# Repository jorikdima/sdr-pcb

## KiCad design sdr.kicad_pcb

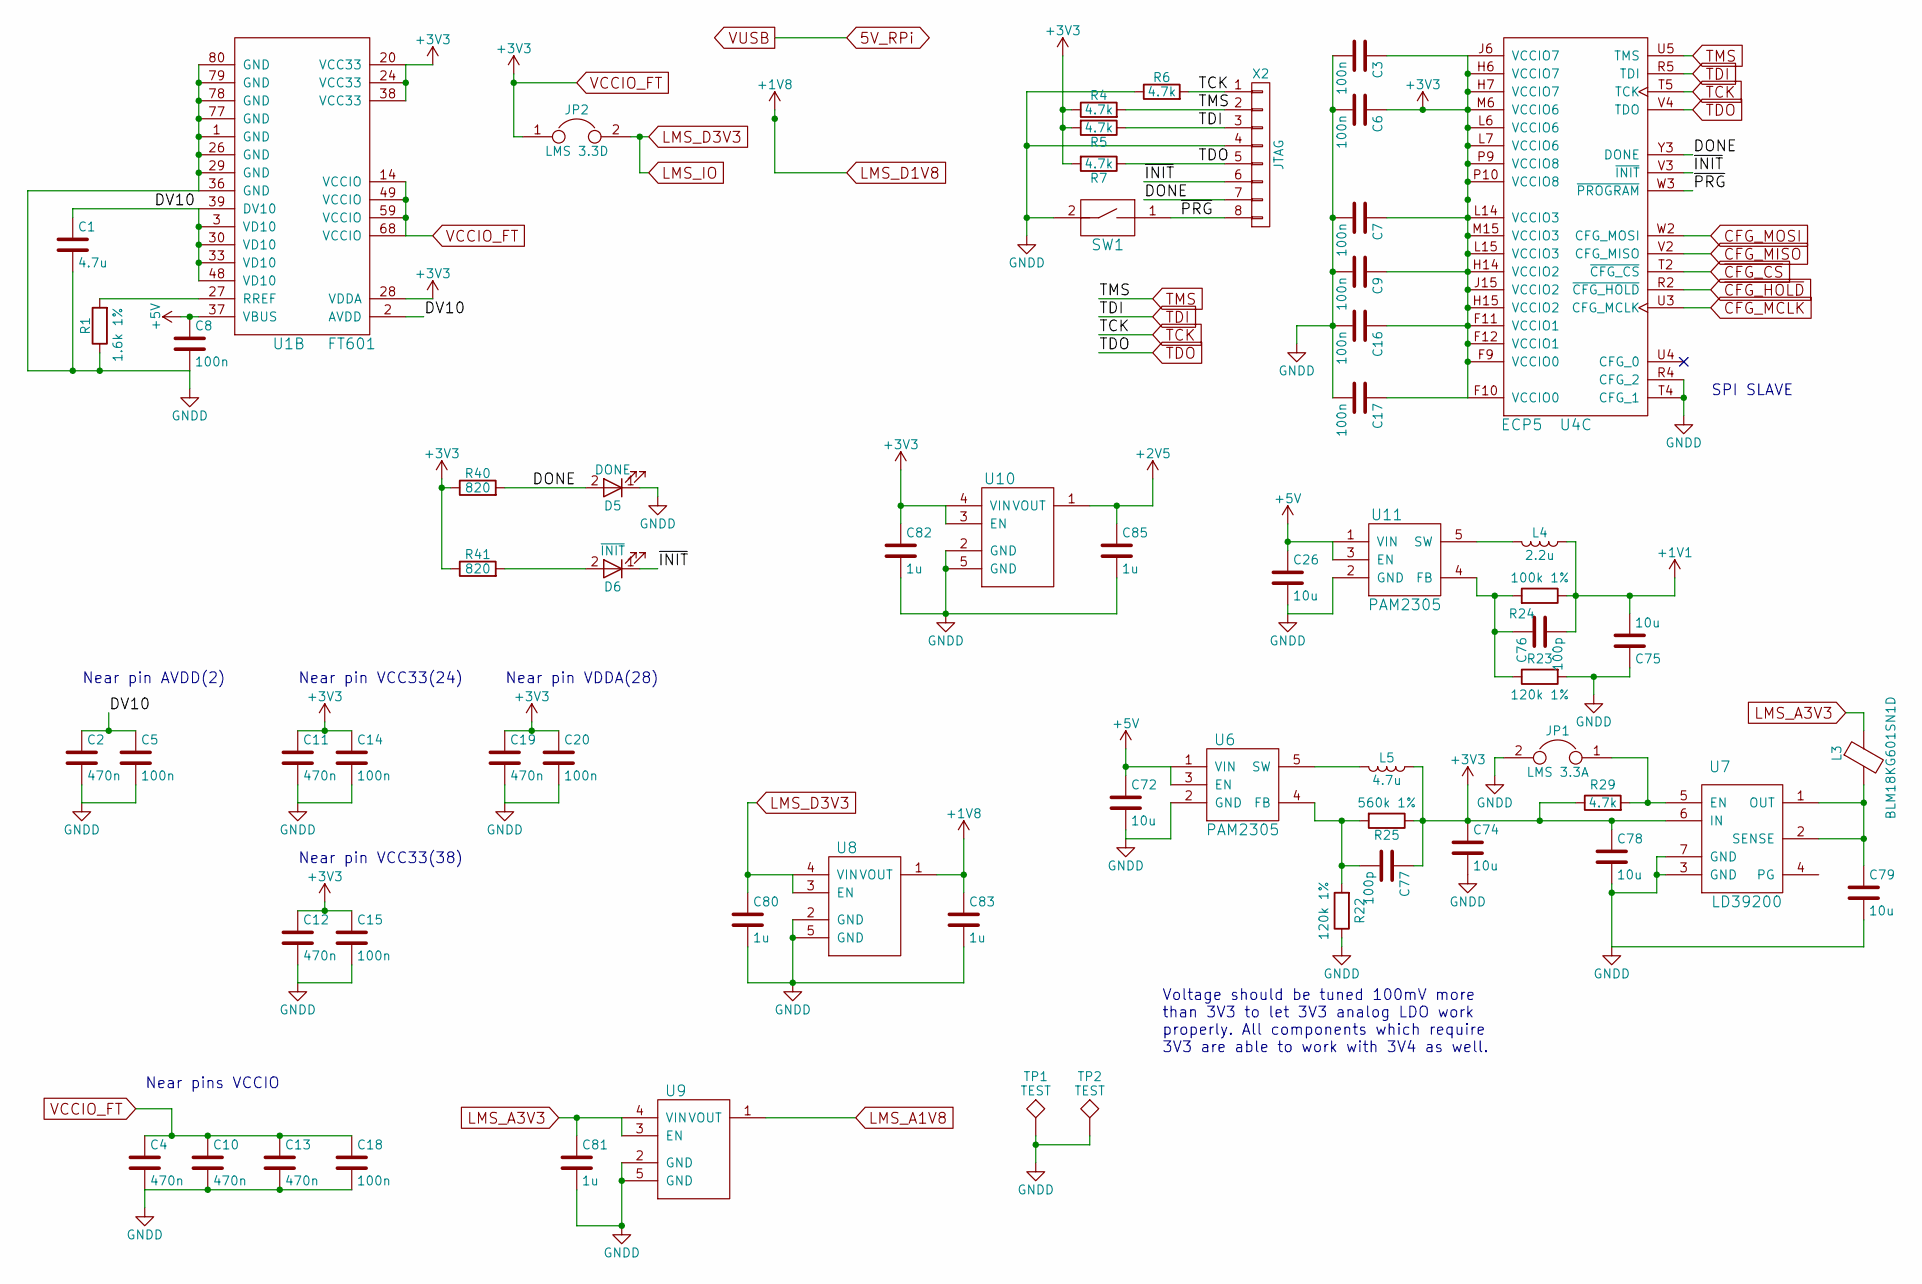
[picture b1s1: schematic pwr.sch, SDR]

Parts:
C1: 4.7u; C_0603
C2, C4, C10, C11, C12, C13, C19: 470n; C_0603
C3, C5, C6, C7, C8, C9, C14, C15, C16, C17, C18, C20: 100n; C_0603
C26, C72, C74, C75, C78, C79: 10u; C_0805
C76, C77: 100p; C_0603
C80, C81, C82, C83, C85: 1u; C_0603
D5: DONE; LED_0603
D6: ~INIT; LED_0603
JP1: LMS 3.3A; Pin_Header_Angled_1x02_Pitch2.54mm
JP2: LMS 3.3D; Pin_Header_Angled_1x02_Pitch2.54mm
L3: BLM18KG601SN1D; L_0805
L4: 2.2u; Inductor_Taiyo-Yuden_MD-4040
L5: 4.7u; Inductor_Taiyo-Yuden_MD-4040
R1: 1.6k 1%; R_0603
R4, R5, R6, R7, R29: 4.7k; R_0603
R22, R23: 120k 1%; R_0603
R24: 100k 1%; R_0603
R25: 560k 1%; R_0603
R40, R41: 820; R_0603
SW1: KMR231NGLFS; Switch_KMR2
TP1, TP2: TEST; Test_Point_Keystone_5015_Micro-Minature
U1: FT601; QFN_76
U4: ECP5; ECP5_381
U6, U11: PAM2305; SOT-23-5
U7: LD39200; DFN-6-1EP_3x3mm_Pitch0.95mm
U8, U9, U10: MIC94310; DFN-4
X2: JTAG; Pin_Header_Straight_1x08_Pitch1.27mm

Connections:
+1V1: C75.2, C76.2, L4.2, R24.1; also elsewhere on the board
+2V5: C85.1, U10.1 (VOUT); also elsewhere on the board
+5V: C8.1, C26.1, C72.1, U1.37 (VBUS), U6.1 (VIN), U6.3 (EN), U11.1 (VIN), U11.3 (EN); also elsewhere on the board
/Power/DONE: D5.2 (A), R40.2, U4.Y3 (DONE), X2.7
/Power/DV10: C1.1, C2.1, C5.1, U1.2 (AVDD), U1.3 (VD10), U1.30 (VD10), U1.33 (VD10), U1.39 (DV10), U1.48 (VD10)
/Power/~INIT: D6.1 (K), U4.V3 (~INIT), X2.6
/Power/~PRG: SW1.1, U4.W3 (~PROGRAM), X2.8
CFG_MCLK: U4.U3 (CFG_MCLK); also elsewhere on the board
CFG_MISO: U4.V2 (CFG_MISO); also elsewhere on the board
CFG_MOSI: U4.W2 (CFG_MOSI); also elsewhere on the board
FT_GPIO1: U4.T2 (~CFG_CS); also elsewhere on the board
LMS_A1V8: U9.1 (VOUT); also elsewhere on the board
LMS_A3V3: C81.1, L3.1, U9.3 (EN), U9.4 (VIN); also elsewhere on the board
LMS_D1V8: C83.1, U8.1 (VOUT); also elsewhere on the board
LMS_D3V3: C80.1, JP2.2, U8.3 (EN), U8.4 (VIN); also elsewhere on the board
unnamed: C76.1, R23.1, R24.2, U11.4 (FB)
unnamed: C77.2, R22.2, R25.2, U6.4 (FB)
unnamed: C79.1, L3.2, U7.1 (OUT), U7.2 (SENSE)
unnamed: D6.2 (A), R41.2
unnamed: JP1.1, R29.2, U7.5 (EN)
unnamed: L4.1, U11.5 (SW)
unnamed: L5.2, U6.5 (SW)
unnamed: R1.2, U1.27 (RREF)
TCK: R6.2, U4.T5 (TCK), X2.1; also elsewhere on the board
TDI: R5.1, U4.R5 (TDI), X2.3; also elsewhere on the board
TDO: R7.1, U4.V4 (TDO), X2.5; also elsewhere on the board
TMS: R4.2, U4.U5 (TMS), X2.2; also elsewhere on the board
VCCIO_FT: C3.1, C4.1, C6.1, C7.1, C9.1, C10.1, C11.1, C12.1, C13.1, C14.1, C15.1, C16.1, C17.1, C18.1, C19.1, C20.1, C74.1, C77.1, C78.1, C82.1, JP2.1, L5.1, R4.1, R5.2, R7.2, R25.1, R29.1, R40.1, R41.1, U1.14 (VCCIO), U1.20 (VCC33), U1.24 (VCC33), U1.28 (VDDA), U1.38 (VCC33), U1.49 (VCCIO), U1.59 (VCCIO), U1.68 (VCCIO), U4.F9 (VCCIO0), U4.F10 (VCCIO0), U4.F11 (VCCIO1), U4.F12 (VCCIO1), U4.H6 (VCCIO7), U4.H7 (VCCIO7), U4.H14 (VCCIO2), U4.H15 (VCCIO2), U4.J6 (VCCIO7), U4.J15 (VCCIO2), U4.L6 (VCCIO6), U4.L7 (VCCIO6), U4.L14 (VCCIO3), U4.L15 (VCCIO3), U4.M6 (VCCIO6), U4.M15 (VCCIO3), U4.P9 (VCCIO8), U4.P10 (VCCIO8), U7.6 (IN), U10.3 (EN), U10.4 (VIN); also elsewhere on the board
~CFG_HOLD: U4.R2 (~CFG_HOLD); also elsewhere on the board

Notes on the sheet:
Near pin AVDD(2)
Near pin VCC33(38)
Near pin VDDA(28)
Near pin VCC33(24)
Near pins VCCIO
SPI SLAVE
Voltage should be tuned 100mV more than 3V3 to let 3V3 analog LDO work properly. All components which require 3V3 are able to work with 3V4 as well.

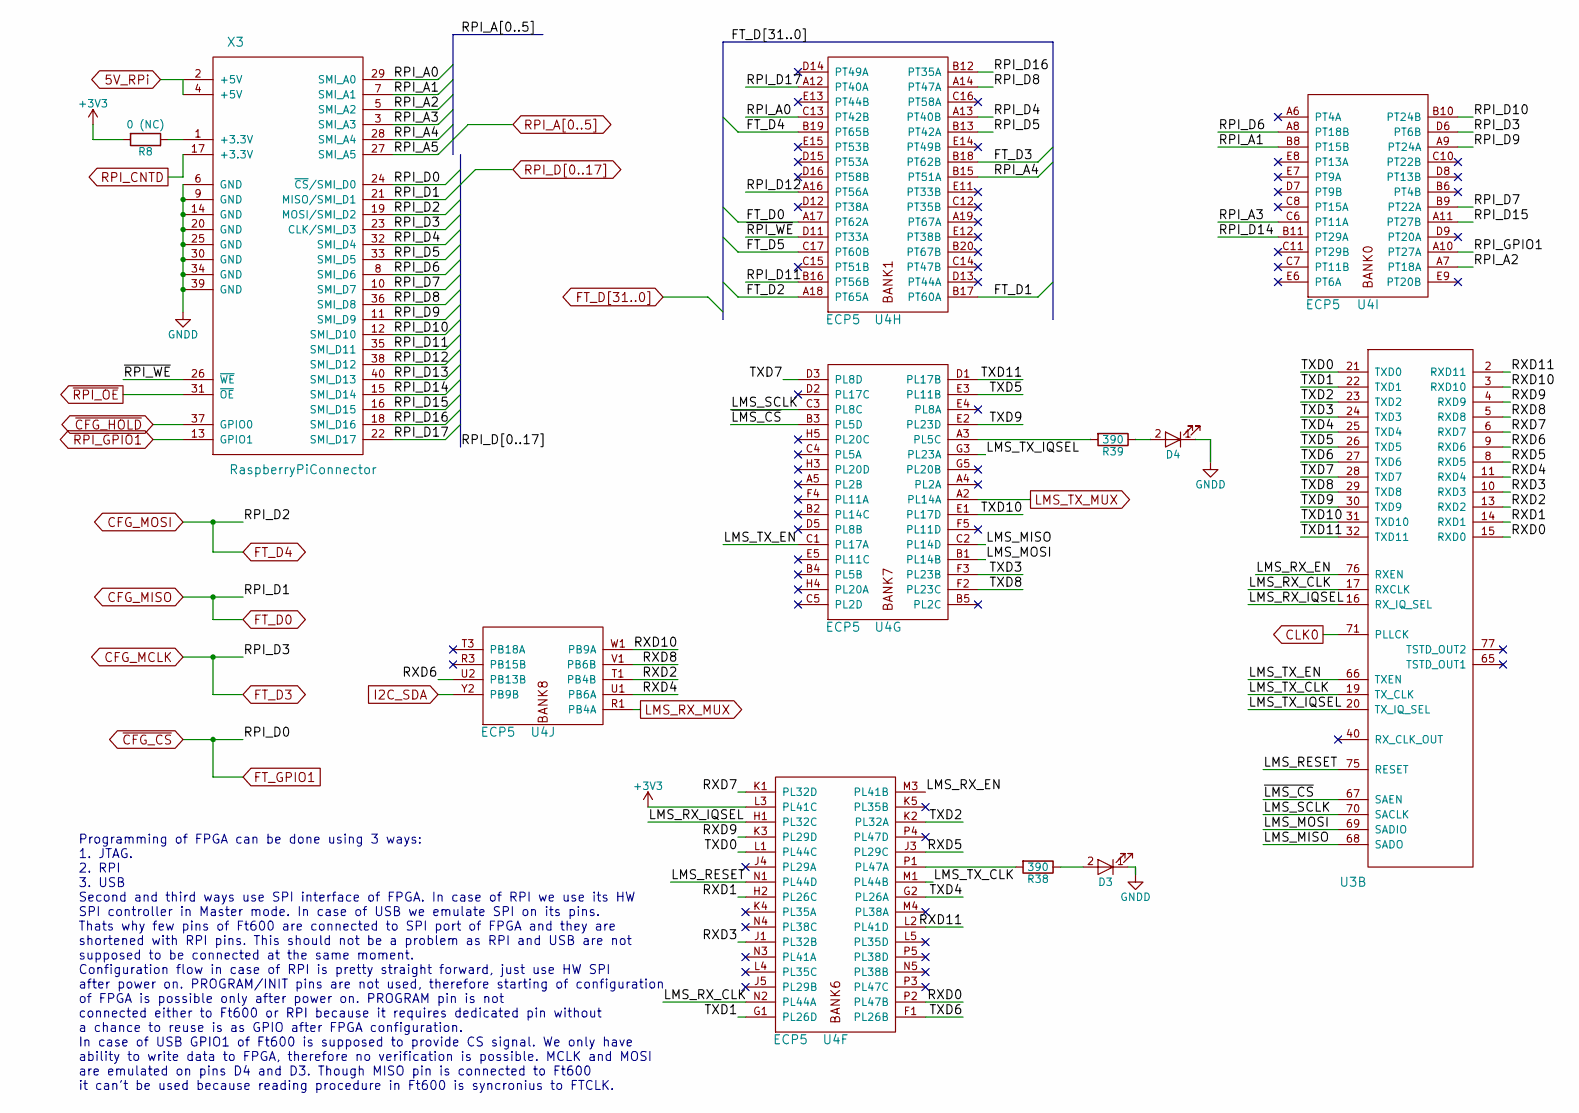
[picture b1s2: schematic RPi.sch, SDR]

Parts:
D3: 5512509F; LED_IND_SINGLE
D4: 5510209F; LED_IND_SINGLE
R8: 0 (NC); R_0603
R38, R39: 390; R_0603
U3: LMS6002DR2; DQFN-120_via_off_pad
U4: ECP5; ECP5_381
X3: RaspberryPiConnector; Socket_Strip_Straight_2x20_Pitch2.54mm

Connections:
/RPi/LMS/LMS_MISO: U3.68 (SADO), U4.C2 (PL14D)
/RPi/LMS/LMS_MOSI: U3.69 (SADIO), U4.B1 (PL14B)
/RPi/LMS/LMS_RESET: U3.75 (RESET), U4.N1 (PL44D)
/RPi/LMS/LMS_RX_CLK: U3.17 (RXCLK), U4.N2 (PL44A)
/RPi/LMS/LMS_RX_EN: U3.76 (RXEN), U4.M3 (PL41B)
/RPi/LMS/LMS_RX_IQSEL: U3.16 (RX_IQ_SEL), U4.H1 (PL32C)
/RPi/LMS/LMS_SCLK: U3.70 (SACLK), U4.C3 (PL8C)
/RPi/LMS/LMS_TX_CLK: U3.19 (TX_CLK), U4.M1 (PL44B)
/RPi/LMS/LMS_TX_EN: U3.66 (TXEN), U4.C1 (PL17A)
/RPi/LMS/LMS_TX_IQSEL: U3.20 (TX_IQ_SEL), U4.G3 (PL23A)
/RPi/LMS/RXD0: U3.15 (RXD0), U4.P2 (PL47B)
/RPi/LMS/RXD1: U3.14 (RXD1), U4.H2 (PL26C)
/RPi/LMS/RXD2: U3.13 (RXD2), U4.T1 (PB4B)
/RPi/LMS/RXD3: U3.10 (RXD3), U4.J1 (PL32B)
/RPi/LMS/RXD4: U3.11 (RXD4), U4.U1 (PB6A)
/RPi/LMS/RXD5: U3.8 (RXD5), U4.J3 (PL29C)
/RPi/LMS/RXD6: U3.9 (RXD6), U4.U2 (PB13B)
/RPi/LMS/RXD7: U3.6 (RXD7), U4.K1 (PL32D)
/RPi/LMS/RXD8: U3.5 (RXD8), U4.V1 (PB6B)
/RPi/LMS/RXD9: U3.4 (RXD9), U4.K3 (PL29D)
/RPi/LMS/RXD10: U3.3 (RXD10), U4.W1 (PB9A)
/RPi/LMS/RXD11: U3.2 (RXD11), U4.L2 (PL41D)
/RPi/LMS/TXD0: U3.21 (TXD0), U4.L1 (PL44C)
/RPi/LMS/TXD1: U3.22 (TXD1), U4.G1 (PL26D)
/RPi/LMS/TXD2: U3.23 (TXD2), U4.K2 (PL32A)
/RPi/LMS/TXD3: U3.24 (TXD3), U4.F3 (PL23B)
/RPi/LMS/TXD4: U3.25 (TXD4), U4.G2 (PL26A)
/RPi/LMS/TXD5: U3.26 (TXD5), U4.E3 (PL11B)
/RPi/LMS/TXD6: U3.27 (TXD6), U4.F1 (PL26B)
/RPi/LMS/TXD7: U3.28 (TXD7), U4.D3 (PL8D)
/RPi/LMS/TXD8: U3.29 (TXD8), U4.F2 (PL23C)
/RPi/LMS/TXD9: U3.30 (TXD9), U4.E2 (PL23D)
/RPi/LMS/TXD10: U3.31 (TXD10), U4.E1 (PL17D)
/RPi/LMS/TXD11: U3.32 (TXD11), U4.D1 (PL17B)
/RPi/LMS/~LMS_CS: U3.67 (SAEN), U4.B3 (PL5D)
/RPi/LMS/~RPI_WE: U4.D11 (PT33A), X3.26 (~WE)
CFG_MCLK: U4.B18 (PT62B), U4.D6 (PT6B), X3.23 (CLK/SMI_D3); also elsewhere on the board
CFG_MISO: U4.A17 (PT62A), X3.21 (MISO/SMI_D1); also elsewhere on the board
CFG_MOSI: U4.B19 (PT65B), X3.19 (MOSI/SMI_D2); also elsewhere on the board
CLK0: U3.71 (PLLCK); also elsewhere on the board
FT_D1: U4.B17 (PT60A); also elsewhere on the board
FT_D2: U4.A18 (PT65A); also elsewhere on the board
FT_D5: U4.C17 (PT60B); also elsewhere on the board
FT_GPIO1: X3.24 (~CS~/SMI_D0); also elsewhere on the board
I2C_SDA: U4.Y2 (PB9B); also elsewhere on the board
LMS_RX_MUX: U4.R1 (PB4A); also elsewhere on the board
LMS_TX_MUX: U4.A2 (PL14A); also elsewhere on the board
unnamed: D3.2 (A), R38.1
unnamed: D4.2 (A), R39.1
unnamed: R8.1, X3.1 (+3.3V)
unnamed: R38.2, U4.P1 (PL47A)
unnamed: R39.2, U4.A3 (PL5C)
RPI_A0: U4.C13 (PT42B), X3.29 (SMI_A0)
RPI_A1: U4.B8 (PT15B), X3.7 (SMI_A1)
RPI_A2: U4.A7 (PT18A), X3.5 (SMI_A2)
RPI_A3: U4.C6 (PT11A), X3.3 (SMI_A3)
RPI_A4: U4.B15 (PT51A), X3.28 (SMI_A4)
RPI_A5: X3.27 (SMI_A5); also elsewhere on the board
RPI_CNTD: X3.17 (+3.3V); also elsewhere on the board
RPI_D4: U4.A13 (PT40B), X3.32 (SMI_D4)
RPI_D5: U4.B13 (PT42A), X3.33 (SMI_D5)
RPI_D6: U4.A8 (PT18B), X3.8 (SMI_D6)
RPI_D7: U4.B9 (PT22A), X3.10 (SMI_D7)
RPI_D8: U4.A14 (PT47A), X3.36 (SMI_D8)
RPI_D9: U4.A9 (PT24A), X3.11 (SMI_D9)
RPI_D10: U4.B10 (PT24B), X3.12 (SMI_D10)
RPI_D11: U4.B16 (PT56B), X3.35 (SMI_D11)
RPI_D12: U4.A16 (PT56A), X3.38 (SMI_D12)
RPI_D13: X3.40 (SMI_D13); also elsewhere on the board
RPI_D14: U4.B11 (PT29A), X3.15 (SMI_D14)
RPI_D15: U4.A11 (PT27B), X3.16 (SMI_D15)
RPI_D16: U4.B12 (PT35A), X3.18 (SMI_D16)
RPI_D17: U4.A12 (PT40A), X3.22 (SMI_D17)
RPI_GPIO1: U4.A10 (PT27A), X3.13 (GPIO1)
VCCIO_FT: R8.2, U4.L3 (PL41C); also elsewhere on the board
~CFG_HOLD: X3.37 (GPIO0); also elsewhere on the board
~RPI_OE: X3.31 (~OE); also elsewhere on the board

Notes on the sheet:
Programming of FPGA can be done using 3 ways: 1. JTAG. 2. RPI 3. USB Second and third ways use SPI interface of FPGA. In case of RPI we use its HW SPI controller in Master mode. In case of USB we emulate SPI on its pins. Thats why few pins of Ft600 are connected to SPI port of FPGA and they are sho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

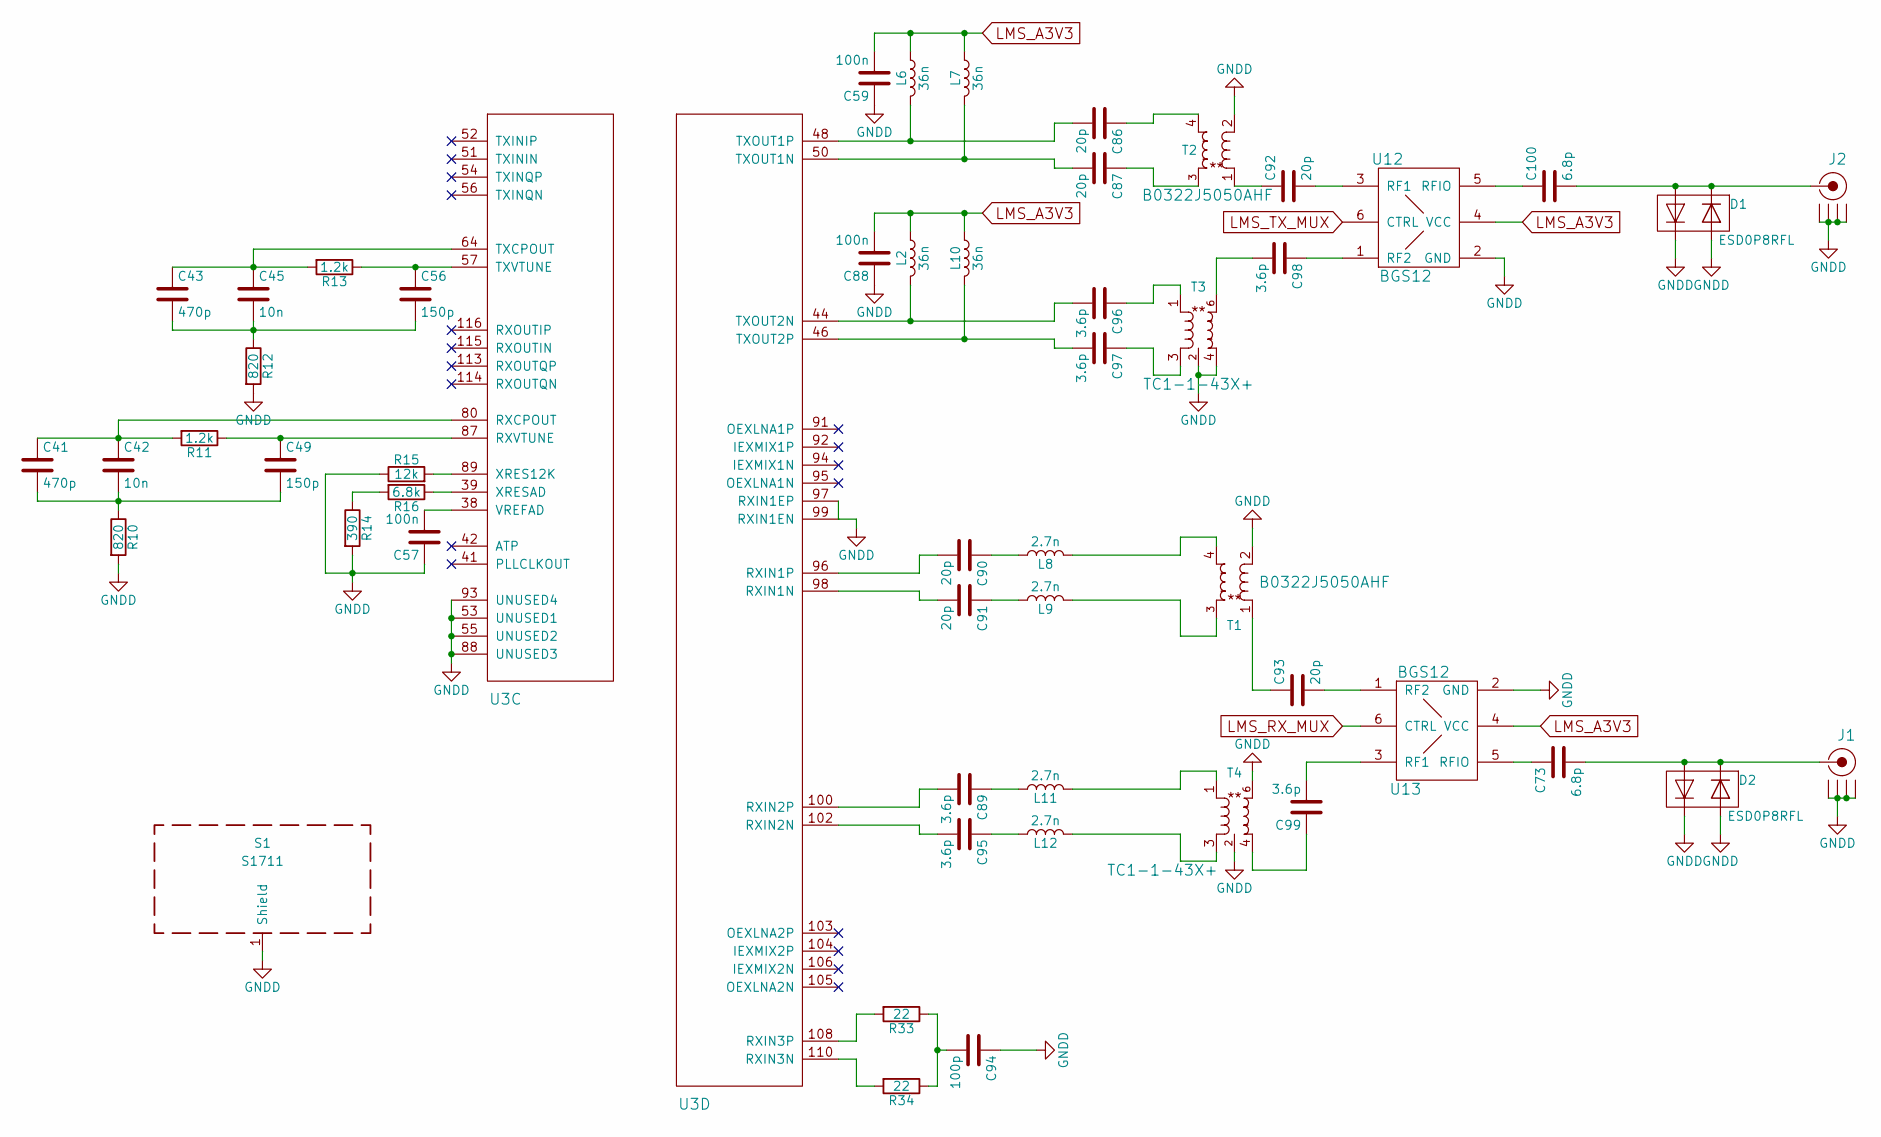
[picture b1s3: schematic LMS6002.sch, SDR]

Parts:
C41, C43: 470p; C_0603
C42, C45: 10n; C_0603
C49, C56: 150p; C_0603
C57, C59, C88: 100n; C_0603
C73, C100: 6.8p; C_0603
C86, C87, C90, C91, C92, C93: 20p; C_0603
C89, C95, C96, C97, C98, C99: 3.6p; C_0603
C94: 100p; C_0603
D1, D2: ESD0P8RFL; TSLP-4-7
J1: RX; SMA_H
J2: TX; SMA_H
L2, L6, L7, L10: 36n; L_0603
L8, L9, L11, L12: 2.7n; L_0603
R10, R12: 820; R_0603
R11, R13: 1.2k; R_0603
R14: 390; R_0603
R15: 12k; R_0603
R16: 6.8k; R_0603
R33, R34: 22; R_0603
S1: S1711; SHIELD
T1, T2: B0322J5050
T3, T4: TR_TC1-1-43X+; TC1-1-43X+; Manufacturer Part Number TC1-1-43X+
U3: LMS6002DR2; DQFN-120_via_off_pad; Manufacturer Part Number LMS6002DFN
U12, U13: BGS12; TSLP-6-4

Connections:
LMS_A3V3: C59.2, C88.2, L2.1, L6.1, L7.1, L10.1, U12.4 (VCC), U13.4 (VCC); also elsewhere on the board
LMS_RX_MUX: U13.6 (CTRL); also elsewhere on the board
LMS_TX_MUX: U12.6 (CTRL); also elsewhere on the board
unnamed: C41.1, C42.1, R11.2, U3.80 (RXCPOUT)
unnamed: C41.2, C42.2, C49.2, R10.1
unnamed: C43.1, C45.1, R13.2, U3.64 (TXCPOUT)
unnamed: C43.2, C45.2, C56.2, R12.1
unnamed: C49.1, R11.1, U3.87 (RXVTUNE)
unnamed: C56.1, R13.1, U3.57 (TXVTUNE)
unnamed: C57.2, U3.38 (VREFAD)
unnamed: C73.1, U13.5 (RFIO)
unnamed: C86.1, T2.4
unnamed: C86.2, L6.2, U3.48 (TXOUT1P)
unnamed: C87.1, T2.3
unnamed: C87.2, L7.2, U3.50 (TXOUT1N)
unnamed: C89.1, L11.1
unnamed: C89.2, U3.100 (RXIN2P)
unnamed: C90.1, L8.1
unnamed: C90.2, U3.96 (RXIN1P)
unnamed: C91.1, L9.1
unnamed: C91.2, U3.98 (RXIN1N)
unnamed: C92.1, T2.1
unnamed: C92.2, U12.3 (RF1)
unnamed: C93.1, T1.1
unnamed: C93.2, U13.1 (RF2)
unnamed: C94.2, R33.1, R34.1
unnamed: C95.1, L12.1
unnamed: C95.2, U3.102 (RXIN2N)
unnamed: C96.1, T3.1
unnamed: C96.2, L2.2, U3.44 (TXOUT2N)
unnamed: C97.1, T3.3
unnamed: C97.2, L10.2, U3.46 (TXOUT2P)
unnamed: C98.1, U12.1 (RF2)
unnamed: C98.2, T3.6
unnamed: C99.1, T4.4
unnamed: C99.2, U13.3 (RF1)
unnamed: C100.1, U12.5 (RFIO)
unnamed: L8.2, T1.4
unnamed: L9.2, T1.3
unnamed: L11.2, T4.1
unnamed: L12.2, T4.3
unnamed: R14.1, R16.2
unnamed: R15.2, U3.89 (XRES12K)
unnamed: R16.1, U3.39 (XRESAD)
unnamed: R33.2, U3.108 (RXIN3P)
unnamed: R34.2, U3.110 (RXIN3N)

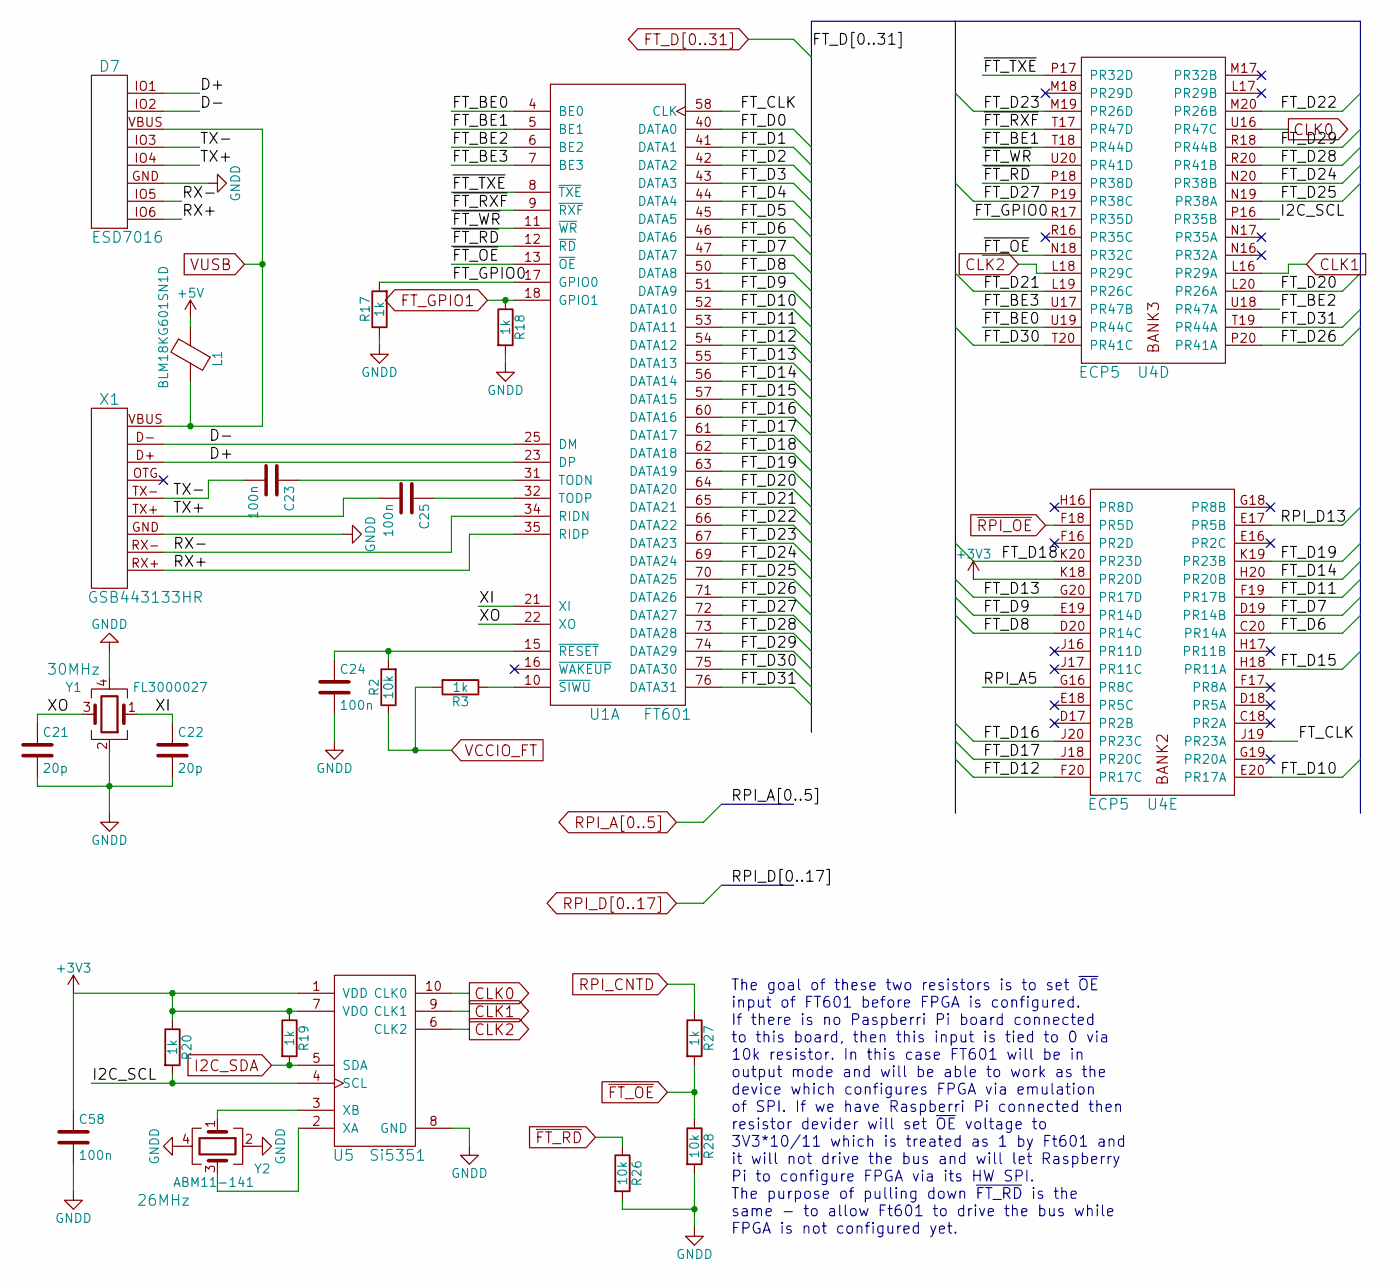
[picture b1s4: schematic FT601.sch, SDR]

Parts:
C21, C22: 20p; C_0603
C23, C24, C25, C58: 100n; C_0603
D7: ESD7016
L1: BLM18KG601SN1D; L_0805
R2, R26, R28: 10k; R_0603
R3, R17, R18, R19, R20, R27: 1k; R_0603
U1: FT601; QFN_76
U4: ECP5; ECP5_381
U5: Si5351; MSOP-10_3x3mm_Pitch0.5mm
X1: GSB443133HR; USB3_microB
Y1: FL3000027; Crystal_SMD_3225-4pin_3.2x2.5mm
Y2: ABM11-141; Crystal_SMD_2016-4pin_2.0x1.6mm

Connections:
+5V: L1.2; also elsewhere on the board
/FT601/D+: D7.IO1, U1.23 (DP), X1.D+
/FT601/D-: D7.IO2, U1.25 (DM), X1.D-
/FT601/FT_BE0: U1.4 (BE0), U4.U19 (PR44C)
/FT601/FT_BE1: U1.5 (BE1), U4.T18 (PR44D)
/FT601/FT_BE2: U1.6 (BE2), U4.U18 (PR47A)
/FT601/FT_BE3: U1.7 (BE3), U4.U17 (PR47B)
/FT601/FT_CLK: U1.58 (CLK), U4.J19 (PR23A)
/FT601/FT_GPIO0: R17.2, U1.17 (GPIO0), U4.R17 (PR35D)
/FT601/I2C_SCL: R20.2, U4.P16 (PR35B), U5.4 (SCL)
/FT601/RX+: D7.IO6, U1.35 (RIDP), X1.RX+
/FT601/RX-: D7.IO5, U1.34 (RIDN), X1.RX-
/FT601/TX+: C25.2, D7.IO4, X1.TX+
/FT601/TX-: C23.2, D7.IO3, X1.TX-
/FT601/XI: C22.1, U1.21 (XI), Y1.1
/FT601/XO: C21.1, U1.22 (XO), Y1.3
/FT601/~FT_RXF: U1.9 (~RXF), U4.T17 (PR47D)
/FT601/~FT_TXE: U1.8 (~TXE), U4.P17 (PR32D)
/FT601/~FT_WR: U1.11 (~WR), U4.U20 (PR41D)
CFG_MCLK: U1.43 (DATA3); also elsewhere on the board
CFG_MISO: U1.40 (DATA0); also elsewhere on the board
CFG_MOSI: U1.44 (DATA4); also elsewhere on the board
CLK0: U4.U16 (PR47C), U5.10 (CLK0); also elsewhere on the board
CLK1: U4.L16 (PR29A), U5.9 (CLK1)
CLK2: U4.L18 (PR29C), U5.6 (CLK2)
FT_D1: U1.41 (DATA1); also elsewhere on the board
FT_D2: U1.42 (DATA2); also elsewhere on the board
FT_D5: U1.45 (DATA5); also elsewhere on the board
FT_D6: U1.46 (DATA6), U4.C20 (PR14A)
FT_D7: U1.47 (DATA7), U4.D19 (PR14B)
FT_D8: U1.50 (DATA8), U4.D20 (PR14C)
FT_D9: U1.51 (DATA9), U4.E19 (PR14D)
FT_D10: U1.52 (DATA10), U4.E20 (PR17A)
FT_D11: U1.53 (DATA11), U4.F19 (PR17B)
FT_D12: U1.54 (DATA12), U4.F20 (PR17C)
FT_D13: U1.55 (DATA13), U4.G20 (PR17D)
FT_D14: U1.56 (DATA14), U4.H20 (PR20B)
FT_D15: U1.57 (DATA15), U4.H18 (PR11A)
FT_D16: U1.60 (DATA16), U4.J20 (PR23C)
FT_D17: U1.61 (DATA17), U4.J18 (PR20C)
FT_D18: U1.62 (DATA18), U4.K20 (PR23D)
FT_D19: U1.63 (DATA19), U4.K19 (PR23B)
FT_D20: U1.64 (DATA20), U4.L20 (PR26A)
FT_D21: U1.65 (DATA21), U4.L19 (PR26C)
FT_D22: U1.66 (DATA22), U4.M20 (PR26B)
FT_D23: U1.67 (DATA23), U4.M19 (PR26D)
FT_D24: U1.69 (DATA24), U4.N20 (PR38B)
FT_D25: U1.70 (DATA25), U4.N19 (PR38A)
FT_D26: U1.71 (DATA26), U4.P20 (PR41A)
FT_D27: U1.72 (DATA27), U4.P19 (PR38C)
FT_D28: U1.73 (DATA28), U4.R20 (PR41B)
FT_D29: U1.74 (DATA29), U4.R18 (PR44B)
FT_D30: U1.75 (DATA30), U4.T20 (PR41C)
FT_D31: U1.76 (DATA31), U4.T19 (PR44A)
FT_GPIO1: R18.1, U1.18 (GPIO1); also elsewhere on the board
I2C_SDA: R19.2, U5.5 (SDA); also elsewhere on the board
unnamed: C23.1, U1.31 (TODN)
unnamed: C24.1, R2.2, U1.15 (~RESET)
unnamed: C25.1, U1.32 (TODP)
unnamed: R3.1, U1.10 (~SIWU)
unnamed: U5.2 (XA), Y2.3
unnamed: U5.3 (XB), Y2.1
RPI_A5: U4.G16 (PR8C); also elsewhere on the board
RPI_CNTD: R27.1; also elsewhere on the board
RPI_D13: U4.E17 (PR5B); also elsewhere on the board
VCCIO_FT: C58.1, R2.1, R3.2, R19.1, R20.1, U4.K18 (PR20D), U5.1 (VDD), U5.7 (VDO); also elsewhere on the board
~FT_OE: R27.2, R28.1, U1.13 (~OE), U4.N18 (PR32C)
~FT_RD: R26.1, U1.12 (~RD), U4.P18 (PR38D)
~RPI_OE: U4.F18 (PR5D); also elsewhere on the board

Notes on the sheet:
The goal of these two resistors is to set ~OE~ input of FT601 before FPGA is configured. If there is no Paspberri Pi board connected to this board, then this input is tied to 0 via 10k resistor. In this case FT601 will be in output mode and will be able to work as the device which configures FPGA v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

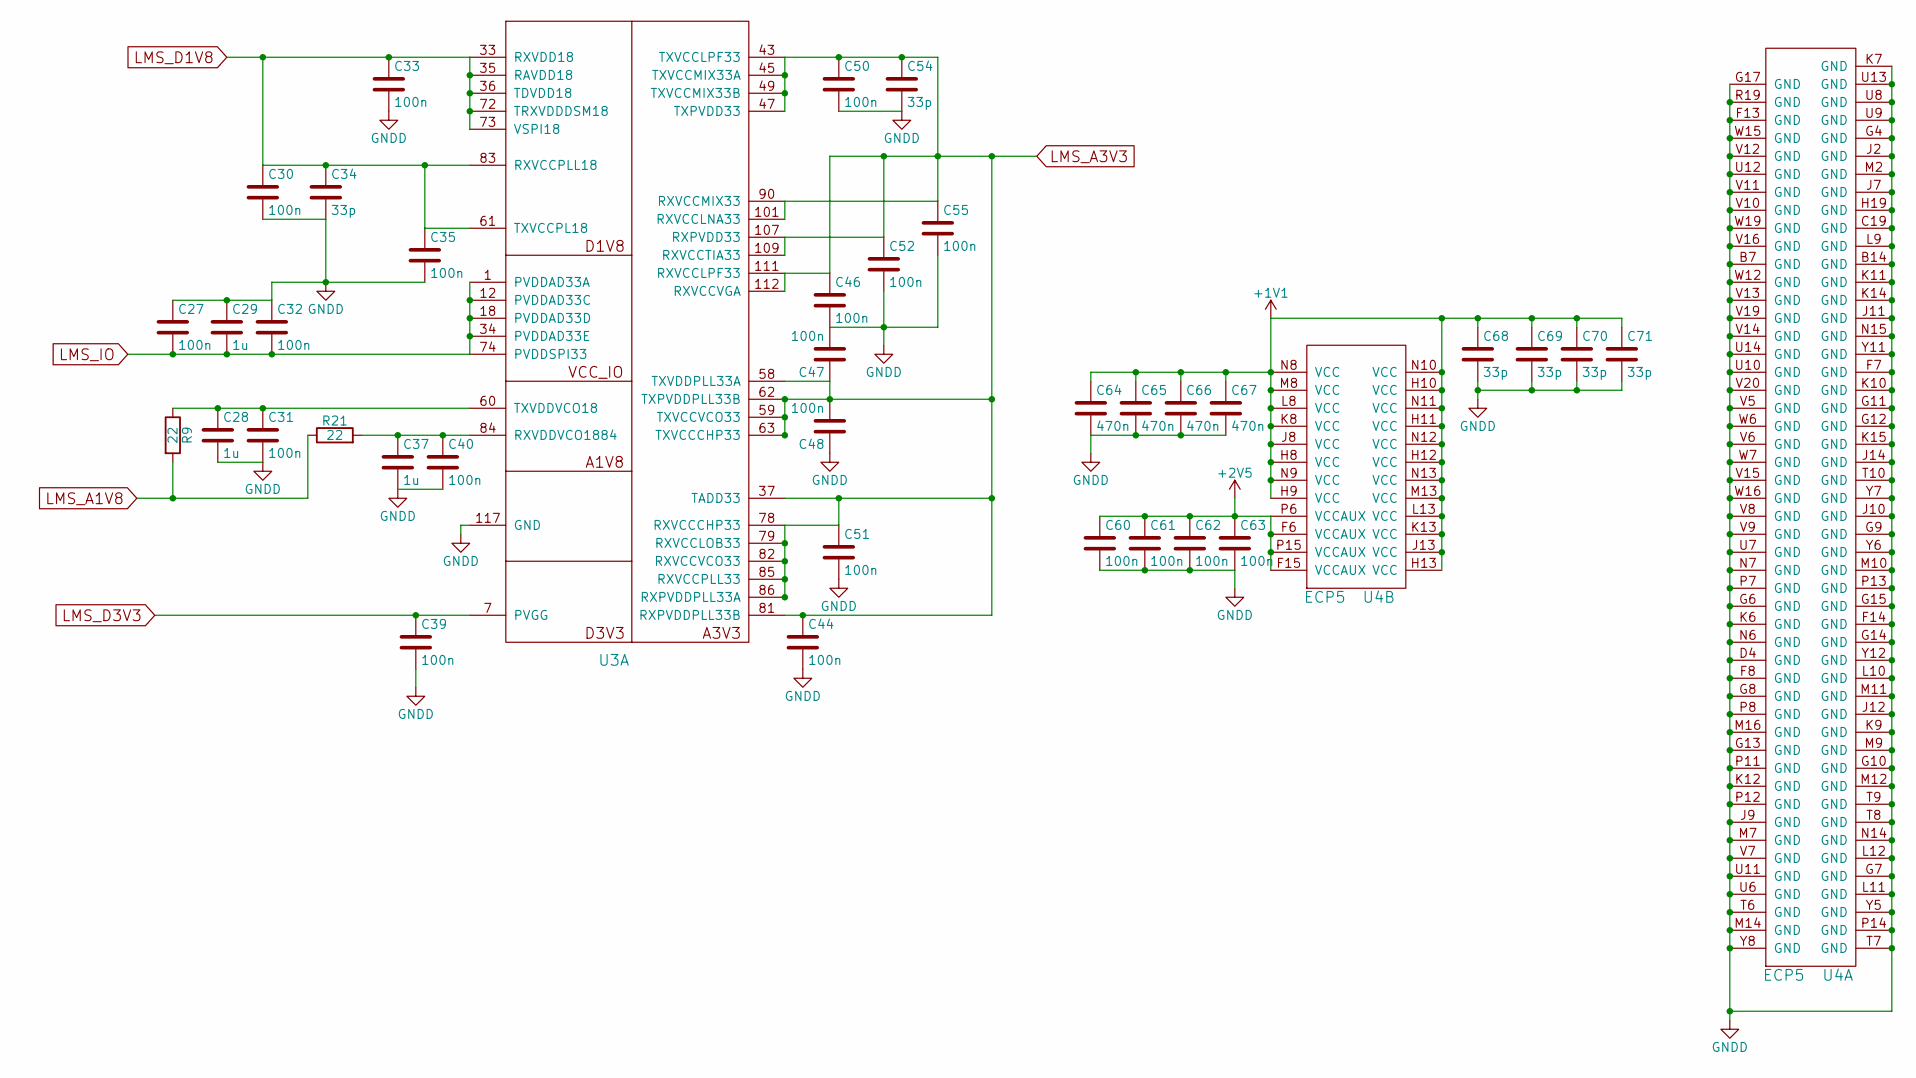
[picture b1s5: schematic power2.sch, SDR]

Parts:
C27, C30, C31, C32, C33, C35, C39, C40, C44, C46, C47, C48, C50, C51, C52, C55, C60, C61, C62, C63: 100n; C_0603
C28, C29, C37: 1u; C_0603
C34, C54, C68, C69, C70, C71: 33p; C_0603
C64, C65, C66, C67: 470n; C_0603
R9, R21: 22; R_0603
U3: LMS6002DR2; DQFN-120_via_off_pad; Manufacturer Part Number LMS6002DFN
U4: ECP5; ECP5_381

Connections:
+1V1: C64.1, C65.1, C66.1, C67.1, C68.1, C69.1, C70.1, C71.1, U4.H8 (VCC), U4.H9 (VCC), U4.H10 (VCC), U4.H11 (VCC), U4.H12 (VCC), U4.H13 (VCC), U4.J8 (VCC), U4.J13 (VCC), U4.K8 (VCC), U4.K13 (VCC), U4.L8 (VCC), U4.L13 (VCC), U4.M8 (VCC), U4.M13 (VCC), U4.N8 (VCC), U4.N9 (VCC), U4.N10 (VCC), U4.N11 (VCC), U4.N12 (VCC), U4.N13 (VCC); also elsewhere on the board
+2V5: C60.1, C61.1, C62.1, C63.1, U4.F6 (VCCAUX), U4.F15 (VCCAUX), U4.P6 (VCCAUX), U4.P15 (VCCAUX); also elsewhere on the board
LMS_A1V8: R9.2, R21.1; also elsewhere on the board
LMS_A3V3: C44.1, C46.1, C47.1, C48.2, C50.1, C51.1, C52.1, C54.1, C55.1, U3.37 (TADD33), U3.43 (TXVCCLPF33), U3.45 (TXVCCMIX33A), U3.47 (TXPVDD33), U3.49 (TXVCCMIX33B), U3.58 (TXVDDPLL33A), U3.59 (TXVCCVCO33), U3.62 (TXPVDDPLL33B), U3.63 (TXVCCCHP33), U3.78 (RXVCCCHP33), U3.79 (RXVCCLOB33), U3.81 (RXPVDDPLL33B), U3.82 (RXVCCVCO33), U3.85 (RXVCCPLL33), U3.86 (RXPVDDPLL33A), U3.90 (RXVCCMIX33), U3.101 (RXVCCLNA33), U3.107 (RXPVDD33), U3.109 (RXVCCTIA33), U3.111 (RXVCCLPF33), U3.112 (RXVCCVGA); also elsewhere on the board
LMS_D1V8: C30.1, C33.1, C34.1, C35.1, U3.33 (RXVDD18), U3.35 (RAVDD18), U3.36 (TDVDD18), U3.61 (TXVCCPL18), U3.72 (TRXVDDDSM18), U3.73 (VSPI18), U3.83 (RXVCCPLL18); also elsewhere on the board
LMS_D3V3: C27.2, C29.2, C32.2, C39.1, U3.1 (PVDDAD33A), U3.7 (PVGG), U3.12 (PVDDAD33C), U3.18 (PVDDAD33D), U3.34 (PVDDAD33E), U3.74 (PVDDSPI33); also elsewhere on the board
unnamed: C28.1, C31.1, R9.1, U3.60 (TXVDDVCO18)
unnamed: C37.1, C40.1, R21.2, U3.84 (RXVDDVCO1884)

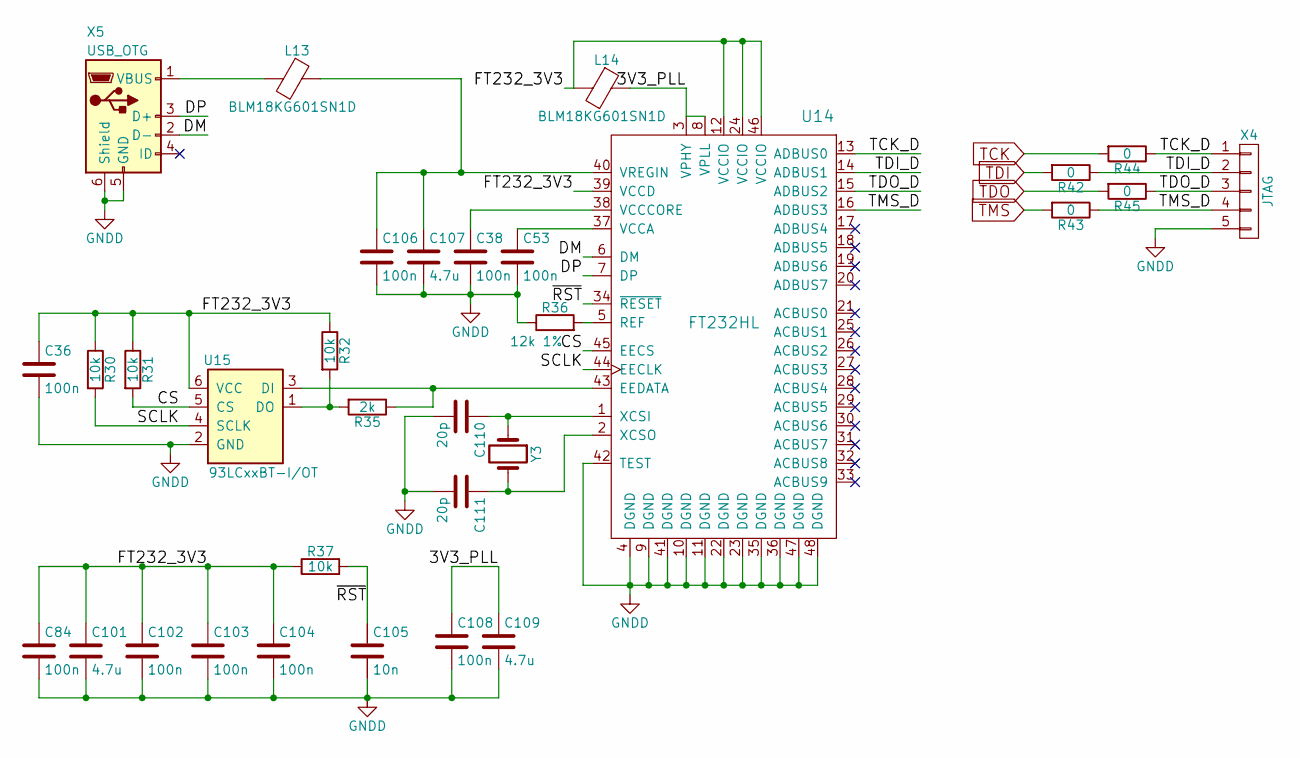
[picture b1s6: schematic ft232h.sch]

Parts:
C36, C38, C53, C84, C102, C103, C104, C106, C108: 100n; C_0603
C101, C107, C109: 4.7u; C_0603
C105: 10n; C_0603
C110, C111: 20p; C_0603
L13, L14: BLM18KG601SN1D; L_0805
R30, R31, R32, R37: 10k; R_0603
R35: 2k; R_0603
R36: 12k 1%; R_0603
R42, R43, R44, R45: 0; R_0603
U14: FT232HL; LQFP-48_7x7mm_Pitch0.5mm
U15: 93LCxxBT-I/OT; SOT-23-6
X4: JTAG; Pin_Header_Straight_1x05_Pitch1.27mm
X5: USB_OTG; USB_Mini-B
Y3: ABLS2-12.000MHZ-D4Y-T; Crystal_HC49-SD_SMD

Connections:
/ft232h/3V3_PLL: C108.1, C109.1, L14.1, U14.3 (VPHY), U14.8 (VPLL)
/ft232h/CS: R31.2, U14.45 (EECS), U15.5 (CS)
/ft232h/DM: U14.6 (DM), X5.2 (D-)
/ft232h/DP: U14.7 (DP), X5.3 (D+)
/ft232h/FT232_3V3: C36.1, C84.1, C101.1, C102.1, C103.1, C104.1, L14.2, R30.1, R31.1, R32.1, R37.1, U14.12 (VCCIO), U14.24 (VCCIO), U14.39 (VCCD), U14.46 (VCCIO), U15.6 (VCC)
/ft232h/SCLK: R30.2, U14.44 (EECLK), U15.4 (SCLK)
/ft232h/TCK_D: R44.1, U14.13 (ADBUS0), X4.1
/ft232h/TDI_D: R42.1, U14.14 (ADBUS1), X4.2
/ft232h/TDO_D: R45.1, U14.15 (ADBUS2), X4.3
/ft232h/TMS_D: R43.1, U14.16 (ADBUS3), X4.4
/ft232h/~RST: C105.1, R37.2, U14.34 (~RESET)
unnamed: C38.1, U14.38 (VCCCORE)
unnamed: C53.1, U14.37 (VCCA)
unnamed: C106.1, C107.1, L13.1, U14.40 (VREGIN)
unnamed: C110.1, U14.1 (XCSI), Y3.1
unnamed: C111.1, U14.2 (XCSO), Y3.2
unnamed: L13.2, X5.1 (VBUS)
unnamed: R32.2, R35.2, U15.1 (DO)
unnamed: R35.1, U14.43 (EEDATA), U15.3 (DI)
unnamed: R36.2, U14.5 (REF)
TCK: R44.2; also elsewhere on the board
TDI: R42.2; also elsewhere on the board
TDO: R45.2; also elsewhere on the board
TMS: R43.2; also elsewhere on the board

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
